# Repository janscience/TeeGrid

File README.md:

# TeeGrid

Record electric fish with electrode arrays based on
[Teensy](https://www.pjrc.com/teensy/) microcontrollers.

Based on the [TeeRec](https://github.com/janscience/TeeRec) library,
inspired by Stefan Mucha's
[EOD-Logger](https://github.com/muchaste/EOD-Logger), the
[MicroConfig](https://github.com/janscience/MicroConfig) library, the
[ESensors](https://github.com/janscience/ESensors) library, and the
[Teensy_Amp](https://github.com/janscience/Teensy_Amp) amplifiers.

## R4 logger with sensors

Logger for 2 to 16 channels based on
[Teensy_Amp R4.1](https://github.com/janscience/Teensy_Amp/tree/main/R4.1) or
[Teensy_Amp R4.2](https://github.com/janscience/Teensy_Amp/tree/main/R4.2) with additional environmental sensors. [Read more](examples/R4-sensors-logger/).

## R4 logger

Logger for 2 to 16 channels based on
[Teensy_Amp R4.1](https://github.com/janscience/Teensy_Amp/tree/main/R4.1) or
[Teensy_Amp R4.2](https://github.com/janscience/Teensy_Amp/tree/main/R4.2). [Read
more](examples/R4-logger/).

## R40 logger

Logger for 2 to 8 channels based on [Teensy_Amp
  R4.0](https://github.com/janscience/Teensy_Amp/tree/main/R4.0). [Read
  more](examples/R40-logger/).

## 8-channel logger

Logger for 8 channels based on [Teensy_Amp
  R1.0](https://github.com/muchaste/Teensy_Amp/tree/main/R1.0).  [Read
  more](examples/8channel-logger/).

## 8-channel logger with sensors

A variant of the [8-channel logger](8channel-logger/) that
supports a variety of environmental sensors. [Read
more](examples/8channel-sensors-logger/).

## Configuration and testing GUI

The [`loggerconf`](utils/loggerconf.py) GUI allows you to configure
the loggers, set the real-time clock, and provides many diagnostic features.

You need to install `pymicroconfig` first, as described
[here](https://github.com/janscience/MicroConfig/tree/main/pymicroconfig).

And you need to install [`pyqtgraph`](https://www.pyqtgraph.org/):
```
pip install pyqtgraph
```

Then navigate to `Arduion/libraries/TeeGrid/utils` and run
```
python loggerconf.py
```

## Housings

- [PVC-tube housings](doc/pvc-tube-housing)

## Electrodes

- [Stainless-steel electrodes](doc/steel-electrodes)

## Installation

- [Installation instructions](doc/installation) for the TeeGrid
  library and sketches.

## Resources

Ideas to solve the syncrhonization problem of multiple loggers:

- [Low-cost synchronization of high-speed audio and video recordings
  in bio-acoustic experiments](https://doi.org/10.1242/jeb.173724)
- [Bio-acoustic tracking and localization using heterogeneous,
  scalable microphone
  arrays](https://doi.org/10.1038/s42003-021-02746-2)

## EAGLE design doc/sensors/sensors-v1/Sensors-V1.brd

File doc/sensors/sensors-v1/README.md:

# Sensors V1

Temperature and illumination sensors and status LEDs for
[R4-sensors-logger](../../../examples/R4-sensors-logger).

## Sensors

### Rohm BH1750 ambient light sensor

- [data sheet](https://github.com/janscience/ESensors/blob/main/docs/chips/datasheets/bh1750.pdf)
- [ESensors library](https://github.com/janscience/ESensors/blob/main/docs/chips/bh1750.md)

### TI TMP119 temperature sensor

- [data sheet](https://github.com/janscience/ESensors/blob/main/docs/chips/datasheets/tmp119.pdf)

## Circuit

- [EAGLE schematics file](Sensors-V1.sch)
- [EAGLE circuit board](Sensors-V1.brd)

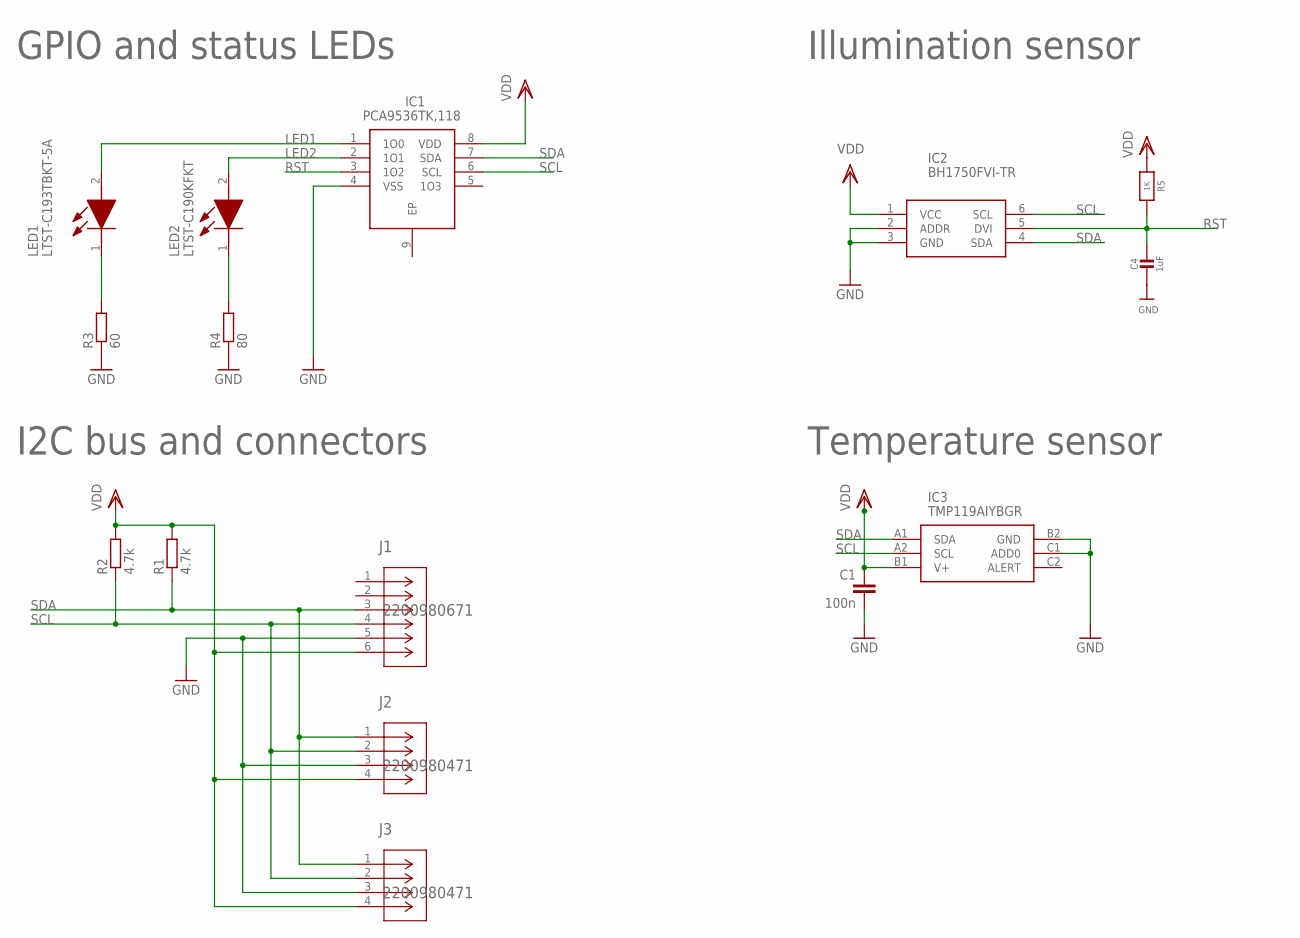
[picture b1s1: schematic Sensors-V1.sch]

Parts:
C1: 100n; C0603
C4: 1uF; 0603-NO
IC1: PCA9536TK,118; SON50P300X300X100-9N
IC2: BH1750FVI-TR; WSOF6
IC3: TMP119AIYBGR; BGA6C40P2X3_95X149X52
J1: 2200980671; CONN_2200980000-SD_06_MOL
J2, J3: 2200980471; CONN_2200980000-SD_04_MOL
LED1: LTST-C193TBKT-5A; LEDC1608X45N
LED2: LTST-C190KFKT; LEDC1607X80N
R1, R2: 4.7k; R0603
R3: 60; R0603
R4: 80; R0603
R5: 1K; 0603-NO

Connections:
GND: C1.2, C4.2, IC1.4 (VSS), IC2.2 (ADDR), IC2.3 (GND), IC3.B2 (GND), IC3.C1 (ADD0), J1.5, J2.3, J3.3, R3.1, R4.1
LED1: IC1.1 (1O0), LED1.2 (A)
LED2: IC1.2 (1O1), LED2.2 (A)
unnamed: LED1.1 (K), R3.2
unnamed: LED2.1 (K), R4.2
RST: C4.1, IC1.3 (1O2), IC2.5 (DVI), R5.2
SCL: IC1.6 (SCL), IC2.6 (SCL), IC3.A2 (SCL), J1.4, J2.2, J3.2, R2.1
SDA: IC1.7 (SDA), IC2.4 (SDA), IC3.A1 (SDA), J1.3, J2.1, J3.1, R1.1
VDD: C1.1, IC1.8 (VDD), IC2.1 (VCC), IC3.B1 (V+), J1.6, J2.4, J3.4, R1.2, R2.2, R5.1

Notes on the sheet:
Temperature sensor
Illumination sensor
GPIO and status LEDs
I2C bus and connectors

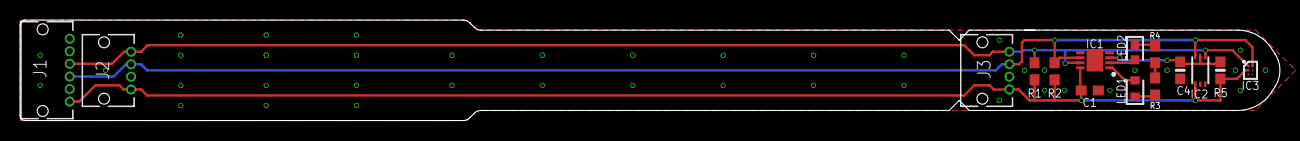
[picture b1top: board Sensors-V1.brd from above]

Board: 2 copper layers, 125.4 x 10.0 mm, 15 parts (0 on the bottom side), 9 nets.

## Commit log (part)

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2024-10-24 fixed PulseFreq and possible sampling rates
2024-10-25 updated SDCardMenu names
2024-10-25 updated Settings
2024-11-21 [loggerconf] started GUI for logger configuration
2024-11-22 [loggerconf] automatically set RTC
2024-11-24 [loggerconf] set RTC on full seconds
2024-11-24 [loggerconf] added request stack
2024-11-24 [loggerconf] fixed RTClock class
2024-11-24 [loggerconf] added logger info
2024-11-24 [loggerconf] added psram info
2024-11-24 [loggerconf] added device to logger info
2024-11-24 [loggerconf] moved time logger info
2024-11-24 [loggerconf] read requests get identifier
2024-11-24 [loggerconf] added file sizes
2024-11-24 [loggerconf] add() functions for adding key-value pairs to layout
2024-11-24 [loggerconf] added SoftwareInfo
2024-11-25 [loggerconf] fixed reconnecting
2024-11-25 [loggerconf] fixed unset menu keysequences
2024-11-26 [loggerconf] added stop string to read requests
2024-11-26 [loggerconf] added list root file button
2024-11-26 [loggerconf] added sd card benchmark
2024-11-27 [loggerconf] fix return for non existing files
2024-11-28 [loggerconf] switch into detailed mode
2024-11-29 [loggerconf] switch off echoing input
2024-11-29 [loggerconf] parsing of input via read_func pointer
2024-11-29 [loggerconf] parsing of parameters
2024-11-30 [loggerconf] improved look and function of parameter widgets
2024-11-30 [loggerconf] added special value
2024-12-01 [loggerconf] moved parsing of instruction to Parameter
2024-12-02 [LoggerFileStorage] set current CPU speed to WaveHeader
2024-12-02 little improvements
2024-12-04 [loggerconf] transmit detcts wrong value and still returns to main menu
2024-12-05 [loggerconf] added configuration actions
2024-12-05 [loggerconf] deal with permission problem, first step...
2024-12-05 [loggerconf] nicely formatted configuration output
2024-12-06 [loggerconf] handling of yes no questions works
2024-12-06 [loggerconf] Message for displaying simple texts
2024-12-07 [loggerconf] added SD card formatting buttons
2024-12-07 [loggerconf] erase all recordings
2024-12-07 [loggerconf] check sd card
2024-12-07 [loggerconf] removed tabwidget
2024-12-07 [loggerconf] added key shortcuts and tooltips
2024-12-07 [loggerconf] verify parameter
2024-12-07 [loggerconf] configuration in QFrame
2024-12-12 [loggerconf] better formated output for load configuration
2024-12-12 [loggerconf] checking and loading works
2024-12-12 [loggerconf] set initial focus
2024-12-13 [loggerconf] fixed erase files
2024-12-13 [loggerconf] check real time clock
2024-12-13 [loggerconf] added run button
2024-12-13 [loggerconf] unified match indicators
2024-12-14 updated checking of number of channels
2024-12-14 [loggerconf] fixed mising unit bug
2024-12-14 [loggerconf] display logger file and presence
2024-12-15 [loggerconf] units as suffix
2024-12-15 [loggerconf] new SpinBox widget with units
2024-12-16 [loggerconf] delete button next to used
2024-12-17 [loggerconf] update terminal only if stream changes
2024-12-17 [R4-logger] improved setting of CPU speed
2024-12-17 removed exactchannels option
2025-01-04 [SensorsLoggerFileStorage] support sensors
2025-01-05 [HardwareActions] report sensor infos
2025-01-05 [loggerconf] added hardware info
2025-01-06 [HardwareActions] base class for ESensors
2025-01-06 [loggerconf] added input devices
2025-01-06 [loggerconf] three column layout
2025-01-10 [R4-logger] added input devices to menu
2025-01-10 [R4-logger] added rtclock devices to diagnostics
2025-01-10 [loggerconf] update for sensor devices
2025-01-10 updated version
2025-01-10 updated version, must be three levels
2025-01-10 [loggerconf] erase recordings updates SD card
2025-01-11 [Logger] renamed from LoggerFileStorage
2025-01-11 [HardwareActions] sensor readings
2025-01-11 [HardwareActions] fixed sensor readings
2025-01-11 [HardwareActions] sensor request
2025-01-11 [loggerconf] display sensor values
2025-01-11 [loggerconf] read in stream as utf8
2025-01-11 [loggerconf] Terminal with monospace font
2025-01-11 [loggerconf] improved reading
2025-01-11 [loggerconf] improved spacing in layout
2025-01-13 [loggerconf] adapted SensorsInfo to removed colon
2025-01-14 [loggerconf] adapted parameter communication
2025-01-15 changed defaults
2025-01-15 [loggerconf] more flexible parameter parsing
2025-01-17 [examples] updated to new firmware upload
2025-01-17 [loggerconf] no benchmark if SD card not present
2025-01-18 [loggerconf] read prompt to the end
2025-01-23 [loggerconf] plot sensor readings with pyqtgraph
2025-01-24 [loggerconf] improved sensors plot
2025-01-27 added input menu
2025-01-28 [loggerconf] plot input data
2025-01-28 [loggerconf] more compact logo
2025-01-29 [loggerconf] improved keyshortcuts for replotting
2025-01-29 [loggerconf] fixed button/label overlap
2025-01-29 [R4-logger] pass controls to input menu
2025-01-29 adapted and added R4SetupPCMs function
2025-01-30 [loggerconf] improved recording plots
2025-02-02 setRateSelection() uses array from ControlPCM186x
2025-02-02 [loggerconf] periodic replot
2025-02-02 [examples] updated gain settings
2025-02-03 [loggerconf] worked on repeated plots
2025-02-04 [loggerconf] use gain and unit for plotting
2025-02-04 [loggerconf] imrpoved plot updating
2025-02-08 added MicroConfig to dependencies
2025-02-09 renamed MicroConfig configure() to execute()
2025-02-09 renamed Configurable to Menu
2025-02-09 [ESensorActions] renamed from HardwareActions
2025-02-11 updated MicroConfig interface
2025-02-12 updated to new Config class
2025-04-02 [loggerconf] updated sensors handling
2025-04-05 [8channel-logger] fixed diagnostic mneu
2025-04-05 [loggerconf] improved plotting key bindings
2025-05-13 [Logger] blink table with ms unit
2025-06-23 [loggerconf] fixed setting of booleans
2025-06-23 [loggerconf] fixed initial delay for setting the RTC
2025-06-23 [loggerconf] started to implement firmware upload
2025-06-24 [loggerconf] firmware upload of a single hex file is working
2025-06-25 [README] added MicroConfig
2025-07-20 [R40-recorder] copied from R40-logger
2025-07-20 [R40-recorder] restructured Logger class
2025-07-21 [Logger] menu also when SD card not present
2025-07-21 [R40-logger] running again
2025-07-31 setup configuration right at the beginning
2025-08-05 [R4-logger] include RTClockDS1307.h
2025-08-05 [R4-logger] simplified power down of CAN
2025-08-09 update to new DiagnosticMenu interface
2025-08-09 [loggerconf] support DeviceID readout
2025-08-11 [R4-sensors-logger] need to initialize sensors before file check
2025-08-11 [R4-sensors-logger] added temperature sensor of real time clock
2025-08-11 [R4-logger] no more backup SD card
2025-08-11 [R4-logger] detect R41b amplifier
2025-08-11 [Logger] print actual working directory
2025-08-11 [loggerconf] adapted to multi directory file lists
2025-08-15 [loggerconf] adapted to listDirectory() file lists
2025-08-18 [Logger] recording path with ID and DATETIME
2025-08-19 [Logger] update
2025-08-22 [examples] names for Blink
2025-08-23 [R4-sensors-logger] added STS40 temperature sensor
2025-08-23 [R4-sensors-logger] light sensor is working
2025-08-23 [R4-sensors-logger] added IR LED
2025-08-23 [R4-sensors-logger] support of three LEDs
2025-08-23 [R4-sensors-logger] switch LEDs on only if no sensor reading
2025-08-23 [R4-sensors-logger] retreive sensor reading only if no LED is on
2025-08-24 [R4-sensors-logger] take blink timeout from settings
2025-08-25 [R4-sensors-logger] added gpio to devices
2025-08-25 [TeeGridBanner] update
2025-08-26 [R4-sensors-logger] changed LED usage
2025-08-31 [R4-sensors-logger] rtc temp first
2025-08-31 [Logger] second status LED has index 1
2025-08-31 [Logger] store blinks file as csv
2025-09-11 [utils] copy data script
2025-09-11 [R4-sensors-logger] update for flona
2025-10-21 [loggerconf] continuous input data update
2025-10-21 [loggerconf] catch exceptions on serial i/o
2025-10-23 [loggerconf] show amplifier infos
2025-10-23 [R4-sensors-logger] increased version
2025-10-29 updated to report functionality
2025-10-29 [loggerconf] updated device id retrieval
2025-10-29 [R4-sensors-logger] better test settings
2025-10-30 [loggerconf] integrated directory cleanup
2025-10-31 [Logger] cleanDir() in check()
2025-10-31 [loggerconf] undefined start sequences are empty lists
2025-10-31 [Logger] start with and without metadata file
2025-10-31 [Logger] filename without extension, hide path and filename
2025-11-02 [loggerconf] export button
2025-11-03 [loggerconf] import is working
2025-11-04 [loggerconf] pass on configuration file name
2025-11-06 [Logger] add metadata from waveheader to ampl_info
2025-11-07 updated MicroConfig execute() and write() interface
2025-11-08 reverted MicroConfig execute() to single stream interface
2025-11-09 Use Menu instead of InfoAction for ampl_info
2025-11-09 [LoggerSettings] new logger settings class
2025-11-10 [Logger] cleanDir() also for backup sd card
2025-11-10 [ESensorsMenu] updated to new MicroConf::execute() interface
2025-11-10 [R4-sensors-logger] added BlinkAction
2025-11-14 [loggerconf] delay between start recording und getting data
2025-11-14 [loggerconf] added EEPROM hexdump
2025-11-14 [loggerconf] make text in terminal selectable
2025-11-14 [loggerconf] made message and question dialog windows
2025-11-14 [loggerconf] made EEPROM put and get available
2025-11-15 [loggerconf] made EEPROM clear available
2025-11-16 [loggerconf] improved code
2025-11-16 fixed roles for ampl_info Menu
2025-11-16 [loggerconf] added LEDs
2025-11-16 [Logger] removed flashLEDs()
2025-11-16 [loggerconf] shortcut for blink test
2025-11-21 [loggerconf] simplified parsing by using gui mode
2025-11-22 [DeviceID] moved from TeeRec
2025-11-22 [DeviceID] added DeviceID action
2025-11-22 [LoggerSettings] updated preparePaths()
2025-11-23 updated to new MicorConfig write() interface
2025-11-23 simplified menus to new MicroConfig roles
2025-11-23 support MicroConfig admin mode
2025-11-24 [loggerconf] show startup messages
2025-11-24 improved startup messages
2025-11-24 [Logger] add metadata to amplifer menu as InfoAction
2025-11-24 [LoggerSettings] possibility to make device id visible in admin mode only
2025-11-24 [Logger] blink timeouts relative to start of recording
2025-11-24 [loggerconf] switching mode sets focus to first parameter
2025-11-25 removed SD card from new DiagnosticMenu
2025-11-26 [loggerconf] load and get are working again
2025-11-27 [loggerconf] hide some actions in user mode
2025-11-27 [loggerconf] fixed visibility of firmware button
2025-11-27 [loggerconf] more imports from microconfig
2025-11-28 [loggerconf] adapted to new Discover class
2025-11-28 [loggerconf] multi logger support
2025-11-29 [loggerconf] moved Parameter to microconfig
2025-11-30 [loggerconf] extracted MicroConfig class to microconfig
2025-11-30 [loggerconf] updated to changes in microconfig
2025-12-02 [loggerconf] updated to new ReportButton interface
2025-12-05 [loggerconf] format without Alt+F
2025-12-08 [Logger] updated to extended cleanDir() interface.
2025-12-12 [loggerconf] smaller plots
2026-01-07 [Logger] fixed handling of random blinks
2026-03-21 [SetupPCM] updated to TeeRec interface change
2026-03-24 [R5-logger] fixed pregain
2026-03-24 [R5-logger] removed deviceid
2026-03-24 [LoggerSettings] device id from device optional
2026-03-25 [Logger] added snooze support
2026-03-26 [Timing] new timing menu
2026-03-26 [R4-snooze-logger] removed
2026-03-26 [R4-sensors-logger] power down PCMs before snooze
2026-03-30 renamed ControlTLV320ADC
2026-04-02 [loggerconf] fixed y-axis scaling
2026-04-02 [R5-logger] configurable channel source
2026-04-07 [SetupTLV] removed debug messages
2026-04-07 [SetupTLV] updated to Input::SOURCE
2026-04-10 [Logger] start immediately if starttime passed
2026-05-07 [loggerconf] cut plot data to same len
2026-05-07 prepare version 1.3.0
2026-05-08 added a first docu about loggerconf
2026-06-01 [SetupPCM] improved setup message with ISC address and TDM data pin
2026-06-04 [SetupPCM] improved setup message
2026-06-05 [R4-sensors-logger] added TDM data pin
2026-06-07 [CANFD] simplified CAN classes to only support CAN FD
2026-06-11 [R5-logger] improvements for first test
2026-06-12 [R5-logger] fixed 32 channel setup
2026-06-13 [SetupTLV] simplified type casts
2026-06-15 [R5-logger] added pregain selection

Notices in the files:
parts and their libraries:
microbuilder: This work is placed in the public domain, and may be freely used for commercial and non-commercial work with the following conditions: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
COPYRIGHT: Copyright (C) 2025 Ultra Librarian. All rights reserved.
